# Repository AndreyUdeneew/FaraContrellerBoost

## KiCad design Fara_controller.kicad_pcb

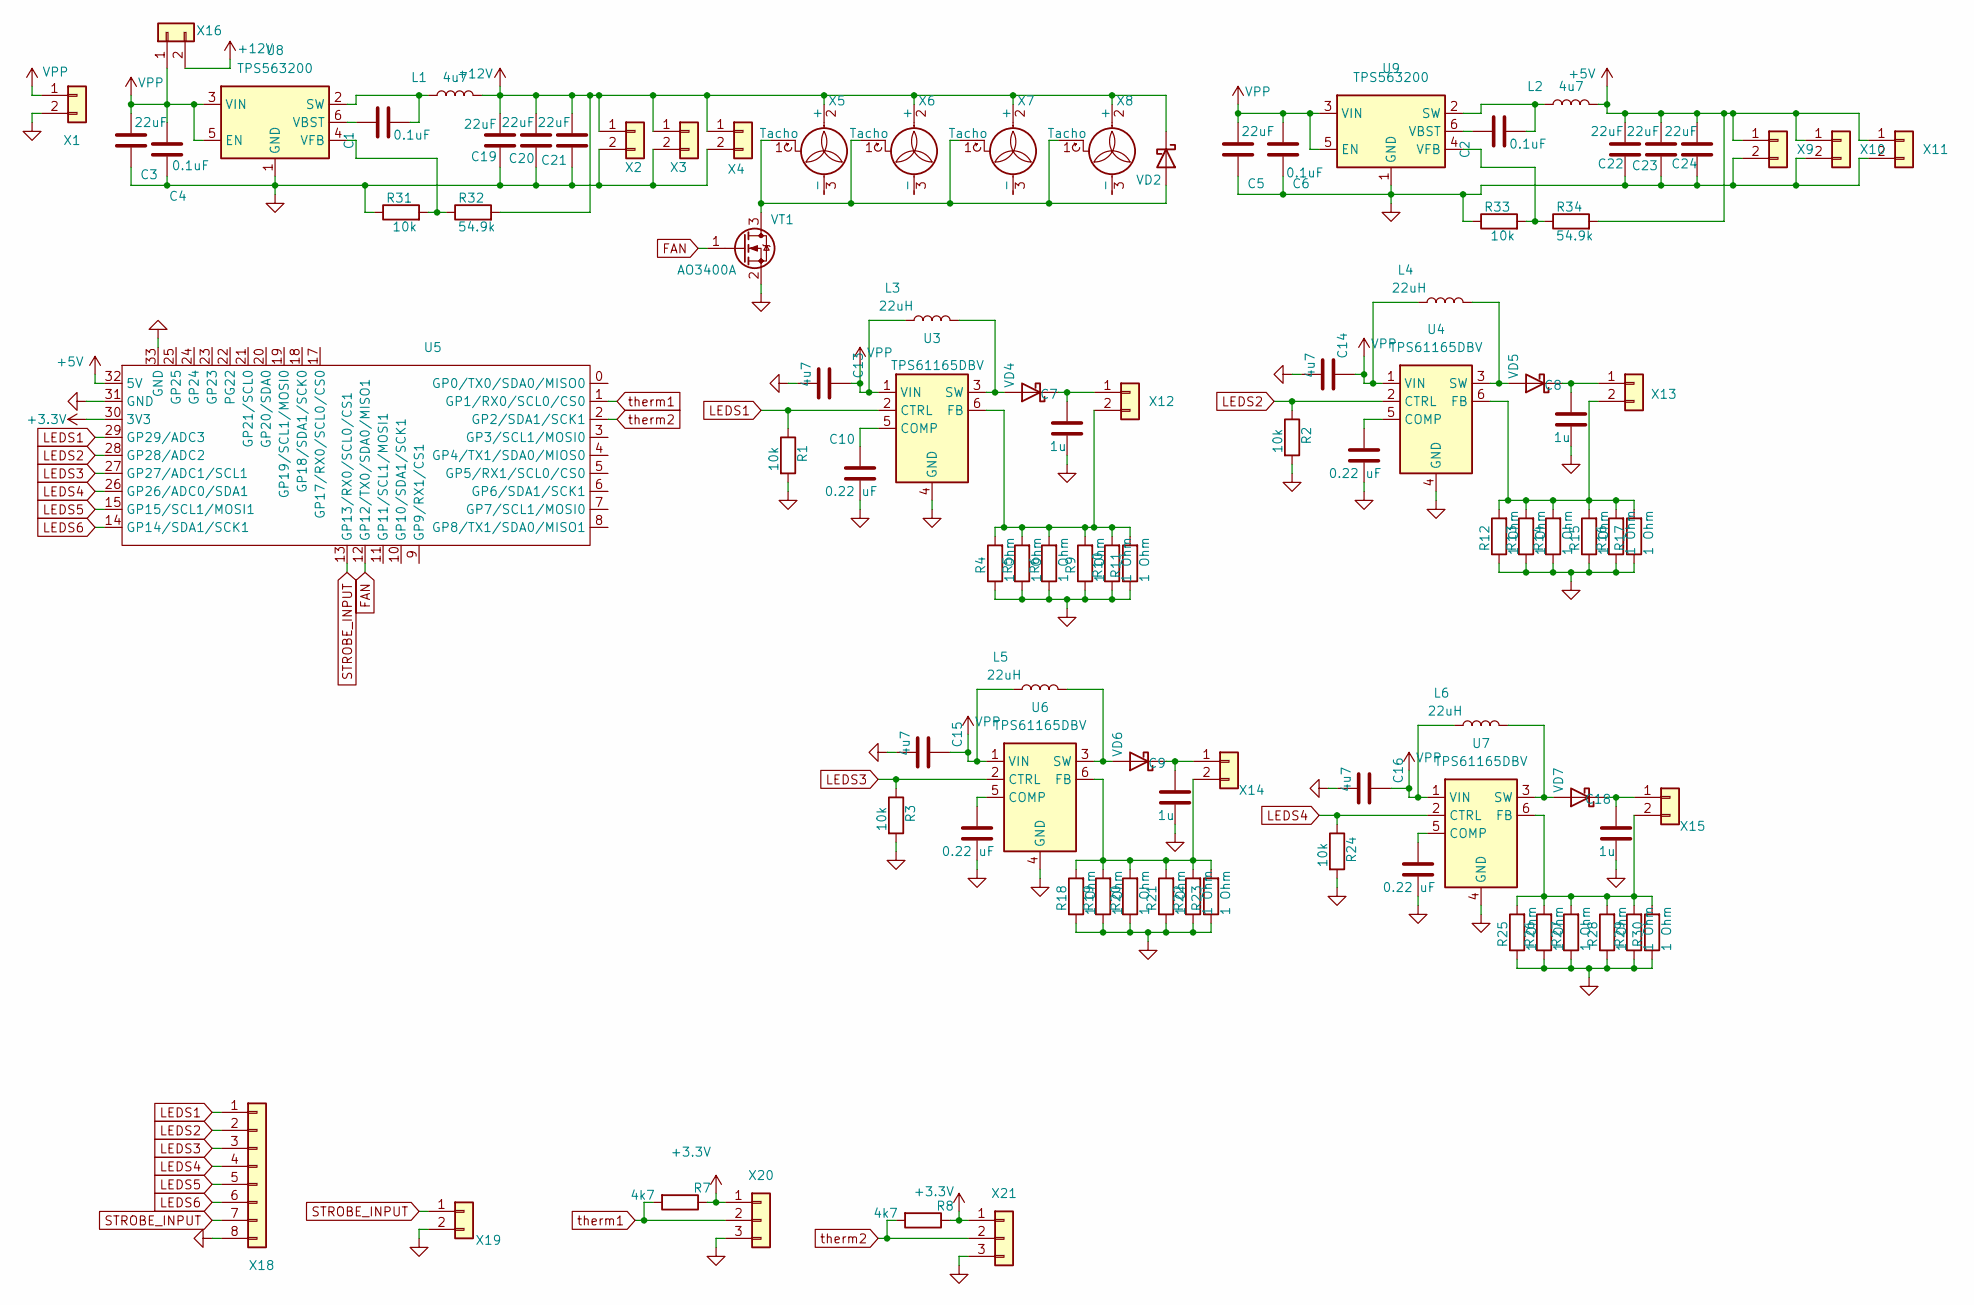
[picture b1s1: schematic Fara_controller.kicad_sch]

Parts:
C1, C2, C4, C6: 0.1uF; C_0603_1608Metric_Pad1.08x0.95mm_HandSolder
C3, C5, C19, C20, C21, C22, C23, C24: 22uF; C_0805_2012Metric_Pad1.18x1.45mm_HandSolder
C7, C8, C9, C18: 1u; C_0603_1608Metric_Pad1.08x0.95mm_HandSolder
C10, C11, C12, C17: 0.22 uF; C_0603_1608Metric_Pad1.08x0.95mm_HandSolder
C13, C14, C15, C16: 4u7; C_0805_2012Metric_Pad1.18x1.45mm_HandSolder
L1, L2: 4u7; L_Chilisin_BMRx00040412
L3, L4, L5, L6: 22uH; L_7.3x7.3_H4.5
R1, R2, R3, R24, R31, R33: 10k; R_0603_1608Metric_Pad0.98x0.95mm_HandSolder
R4, R5, R6, R9, R10, R11, R12, R13, R14, R15, R16, R17, R18, R19, R20, R21, R22, R23, R25, R26, R27, R28, R29, R30: 1 Ohm; R_0603_1608Metric_Pad0.98x0.95mm_HandSolder
R7, R8: 4k7; R_0603_1608Metric_Pad0.98x0.95mm_HandSolder
R32, R34: 54.9k; R_0603_1608Metric_Pad0.98x0.95mm_HandSolder
U3, U4, U6, U7: TPS61165DBV; SOT-23-6
U5: RP2040Zero
U8, U9: TPS563200; SOT-23-6
VD2, VD4, VD5, VD6, VD7: CDBA3100-HF; D_SOD-123
VT1: AO3400A; SOT-23
X1: Conn_01x02; JST_VH_B2P-VH-B_1x02_P3.96mm_Vertical
X2, X3, X4, X9, X10, X11, X12, X13, X14, X15, X16, X19: Conn_01x02; JST_XH_B2B-XH-A_1x02_P2.50mm_Vertical
X5, X6, X7, X8: Fan_3pin; FanPinHeader_1x03_P2.54mm_Vertical
X18: Objective; PinSocket_1x08_P1.27mm_Vertical
X20, X21: Conn_01x03; JST_XH_B3B-XH-A_1x03_P2.50mm_Vertical

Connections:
+3.3V: R7.1, R8.1, U5.30 (3V3), X20.1, X21.1
+5V: C22.2, C23.2, C24.2, L2.2, R34.2, U5.32 (5V), X9.1, X10.1, X11.1
+12V: C19.2, C20.2, C21.2, L1.2, R32.2, VD2.1 (K), X2.1, X3.1, X4.1, X5.2 (+), X6.2 (+), X7.2 (+), X8.2 (+), X16.2
FAN: U5.12 (GP12/TX0/SDA0/MISO1), VT1.1 (G)
GND: C3.1, C4.1, C5.1, C6.1, C7.2, C8.2, C9.2, C10.2, C11.2, C12.2, C13.2, C14.2, C15.2, C16.2, C17.2, C18.2, C19.1, C20.1, C21.1, C22.1, C23.1, C24.1, R1.2, R2.2, R3.2, R4.1, R5.1, R6.1, R9.1, R10.1, R11.1, R12.1, R13.1, R14.1, R15.1, R16.1, R17.1, R18.1, R19.1, R20.1, R21.1, R22.1, R23.1, R24.2, R25.1, R26.1, R27.1, R28.1, R29.1, R30.1, R31.1, R33.1, U3.4 (GND), U4.4 (GND), U5.31 (GND), U5.33 (GND), U6.4 (GND), U7.4 (GND), U8.1 (GND), U9.1 (GND), VT1.2 (S), X1.2, X2.2, X3.2, X4.2, X9.2, X10.2, X11.2, X18.8, X19.2, X20.3, X21.3
LEDS1: R1.1, U3.2 (CTRL), U5.29 (GP29/ADC3), X18.1
LEDS2: R2.1, U4.2 (CTRL), U5.28 (GP28/ADC2), X18.2
LEDS3: R3.1, U5.27 (GP27/ADC1/SCL1), U6.2 (CTRL), X18.3
LEDS4: R24.1, U5.26 (GP26/ADC0/SDA1), U7.2 (CTRL), X18.4
LEDS5: U5.15 (GP15/SCL1/MOSI1), X18.5
LEDS6: U5.14 (GP14/SDA1/SCK1), X18.6
unnamed: C10.1, U3.5 (COMP)
unnamed: R4.2, R5.2, R6.2, R9.2, R10.2, R11.2, U3.6 (FB), X12.2
unnamed: L3.2, U3.3 (SW), VD4.2 (A)
unnamed: C11.1, U4.5 (COMP)
unnamed: R12.2, R13.2, R14.2, R15.2, R16.2, R17.2, U4.6 (FB), X13.2
unnamed: L4.2, U4.3 (SW), VD5.2 (A)
unnamed: C12.1, U6.5 (COMP)
unnamed: R18.2, R19.2, R20.2, R21.2, R22.2, R23.2, U6.6 (FB), X14.2
unnamed: L5.2, U6.3 (SW), VD6.2 (A)
unnamed: C17.1, U7.5 (COMP)
unnamed: R25.2, R26.2, R27.2, R28.2, R29.2, R30.2, U7.6 (FB), X15.2
unnamed: L6.2, U7.3 (SW), VD7.2 (A)
unnamed: C1.2, L1.1, U8.2 (SW)
unnamed: C1.1, U8.6 (VBST)
unnamed: R31.2, R32.1, U8.4 (VFB)
unnamed: C2.2, L2.1, U9.2 (SW)
unnamed: C2.1, U9.6 (VBST)
unnamed: R33.2, R34.1, U9.4 (VFB)
unnamed: VD2.2 (A), VT1.3 (D), X5.1 (Tacho), X6.1 (Tacho), X7.1 (Tacho), X8.1 (Tacho)
unnamed: C7.1, VD4.1 (K), X12.1
unnamed: C8.1, VD5.1 (K), X13.1
unnamed: C9.1, VD6.1 (K), X14.1
unnamed: C18.1, VD7.1 (K), X15.1
STROBE_INPUT: U5.13 (GP13/RX0/SCL0/CS1), X18.7, X19.1
VPP: C3.2, C4.2, C5.2, C6.2, C13.1, C14.1, C15.1, C16.1, L3.1, L4.1, L5.1, L6.1, U3.1 (VIN), U4.1 (VIN), U6.1 (VIN), U7.1 (VIN), U8.3 (VIN), U8.5 (EN), U9.3 (VIN), U9.5 (EN), X1.1, X16.1
therm1: R7.2, U5.1 (GP1/RX0/SCL0/CS0), X20.2
therm2: R8.2, U5.2 (GP2/SDA1/SCK1), X21.2

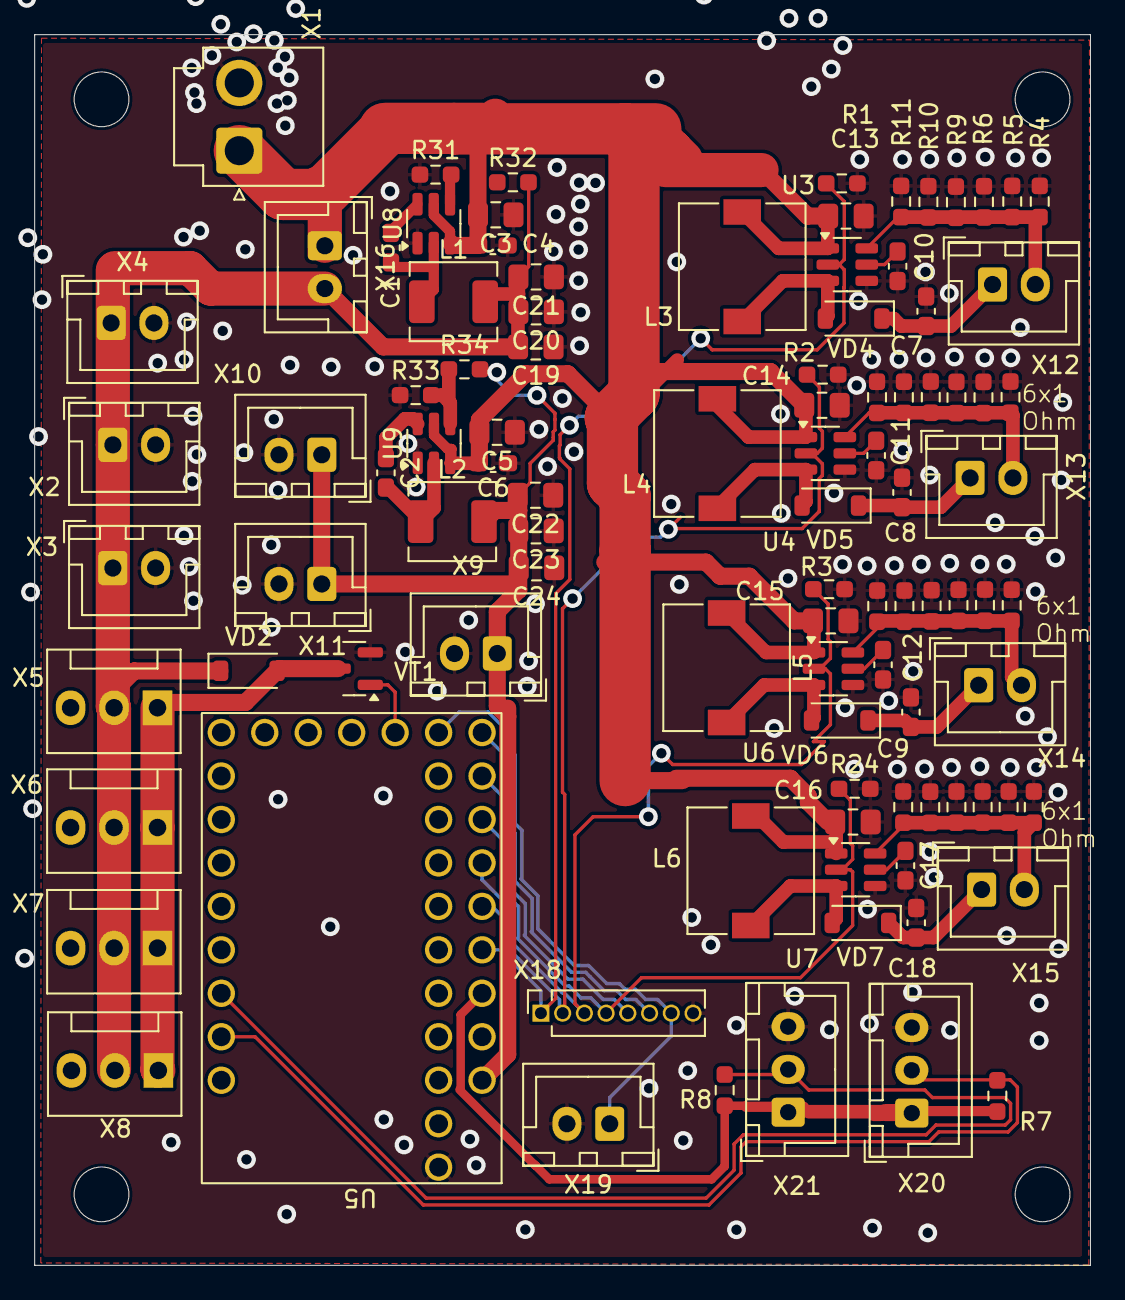
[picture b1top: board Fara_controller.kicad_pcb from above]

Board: 2 copper layers, 61.7 x 71.9 mm, 97 parts (0 on the bottom side), 38 nets.

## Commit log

2025-01-16 v0.1 Circuit was created
2025-01-16 v0.2 draft decomposition was made
2025-01-16 v0.3 4th driver was decomposed
2025-01-16 v0.4 draft routing was completed
2025-01-17 v0.5 actual state
2025-01-17 v0.6 actual state
2025-01-18 v0.7 small changes
2025-01-28 v0.8 compact buck converters were added
2025-03-04 v0.9 small changes
